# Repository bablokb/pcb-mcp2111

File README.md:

A small pcb for the MCP2221 chip
================================

The MCP2221 chip is an USB to GPIO bridge and brings GPIOs (including I2C) to any computer.

This github-repository contains a Kicad-project for the chip:

Status
------

Current status: the pcb was successfully produced
by [https://aisler.net](https://aisler.net):

Hardware
--------

Components for the board:

  - MCP2221/MCP2221A
  - socket
  - two capacitors (required, see datasheet)
  - a micro-sd-female connector (breakout)
  - an AMS1117 5V->3.3V converter (breakout, configurable using jumper-shim)
  - pullups for I2C-pins
  - pullups for GP0-GP3 (configurable using jumper-shims)
  - LEDs for GP0 and GP1 (configurable using jumper-shims)
  - buttons for GP2 and GP3
  - two male-connectors exposing all pins of the MCP2221 (breadboard-friendly spacing)

You can find details in the file `part-list.ods`.

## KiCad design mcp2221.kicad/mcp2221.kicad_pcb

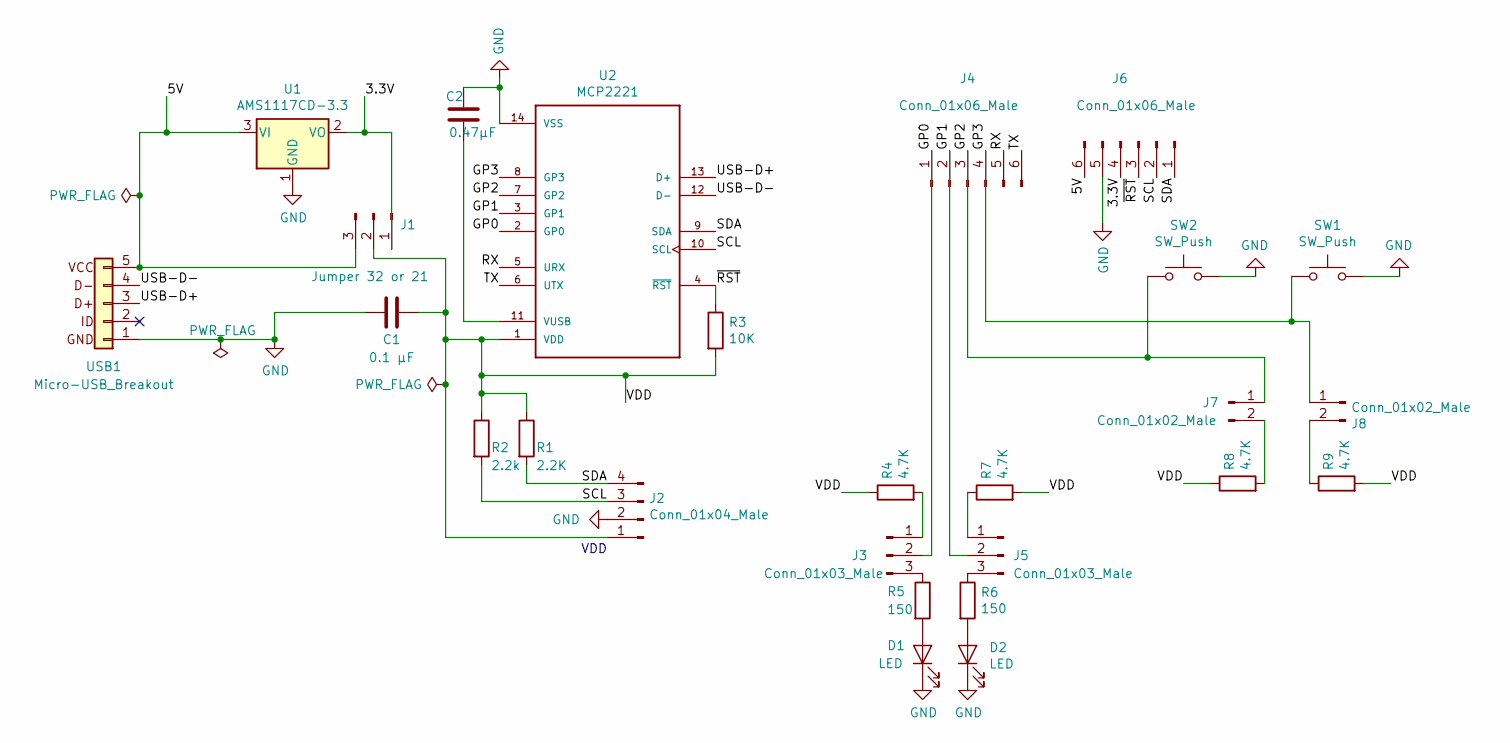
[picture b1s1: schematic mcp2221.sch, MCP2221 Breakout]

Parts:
C1: 0.1 µF; C_1206_3216_Pad1.7x1.75mm_BB
C2: 0.47µF; C_1206_3216_Pad1.7x1.75mm_BB
D1, D2: LED; LED_1206_3216_Pad1.7x1.75mm_BB
J1: Jumper 32 or 21; PinHeader_1x03_P2.54mm_Vertical
J2: Conn_01x04_Male; PinHeader_1x04_P2.54mm_Vertical
J3, J5: Conn_01x03_Male; PinHeader_1x03_P2.54mm_Vertical
J4, J6: Conn_01x06_Male; PinHeader_1x06_P2.54mm_Vertical
J7, J8: Conn_01x02_Male; PinHeader_1x02_P2.54mm_Vertical
R1: 2.2K; R_1206_3216_Pad1.7x1.75mm_BB
R2: 2.2k; R_1206_3216_Pad1.7x1.75mm_BB
R3: 10K; R_1206_3216_Pad1.7x1.75mm_BB
R4, R7, R8, R9: 4.7K; R_1206_3216_Pad1.7x1.75mm_BB
R5, R6: 150; R_1206_3216_Pad1.7x1.75mm_BB
SW1, SW2: SW_Push; SW_Push_1P1T_NO_6x6mm_H9.5mm
U1: AMS1117CD-3.3; AMS1117_Breakout
U2: MCP2221
USB1: Micro-USB_Breakout

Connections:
/3.3V: J1.1, J6.4, U1.2 (VO)
/5V: J1.3, J6.6, U1.3 (VI), USB1.5
/GP0: J3.2, J4.1, U2.2 (GP0)
/GP1: J4.2, J5.2, U2.3 (GP1)
/GP2: J4.3, J7.1, SW2.1, U2.7 (GP2)
/GP3: J4.4, J8.1, SW1.1, U2.8 (GP3)
/RX: J4.5, U2.5 (URX)
/SCL: J2.3, J6.2, R2.2, U2.10 (SCL)
/SDA: J2.4, J6.1, R1.2, U2.9 (SDA)
/TX: J4.6, U2.6 (UTX)
/USB-D+: U2.13 (D+), USB1.3
/USB-D-: U2.12 (D-), USB1.4
/VDD: C1.1, J1.2, J2.1, R1.1, R2.1, R3.2, R4.1, R7.2, R8.1, R9.2, U2.1 (VDD)
/~RST~: J6.3, R3.1, U2.4 (~RST~)
GND: C1.2, C2.2, D1.1 (K), D2.1 (K), J2.2, J6.5, SW1.2, SW2.2, U1.1 (GND), U2.14 (VSS), USB1.1
unnamed: C2.1, U2.11 (VUSB)
unnamed: D1.2 (A), R5.2
unnamed: D2.2 (A), R6.2
unnamed: J3.1, R4.2
unnamed: J3.3, R5.1
unnamed: J5.1, R7.1
unnamed: J5.3, R6.1
unnamed: J7.2, R8.2
unnamed: J8.2, R9.1

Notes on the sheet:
VDD

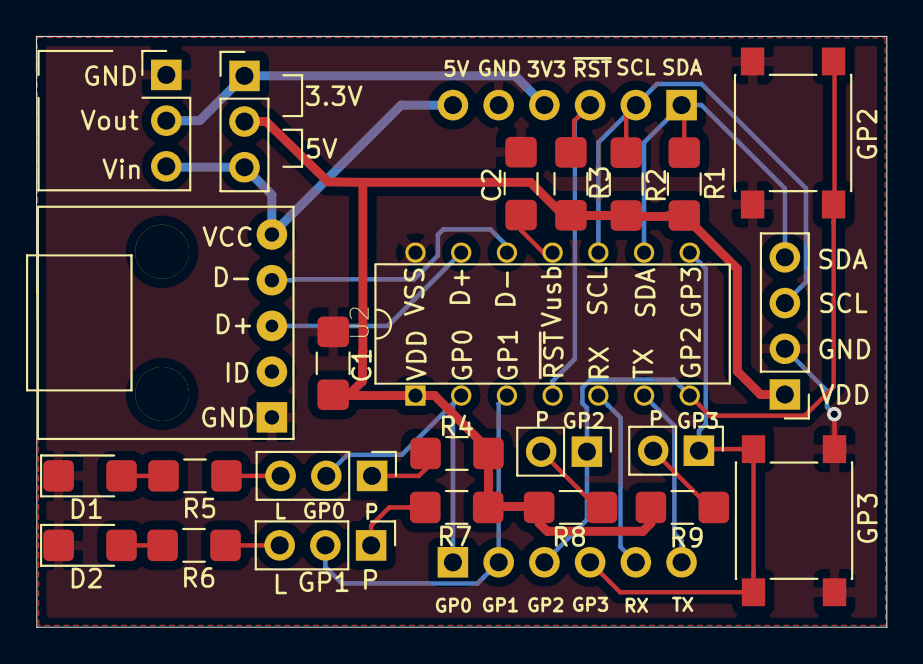
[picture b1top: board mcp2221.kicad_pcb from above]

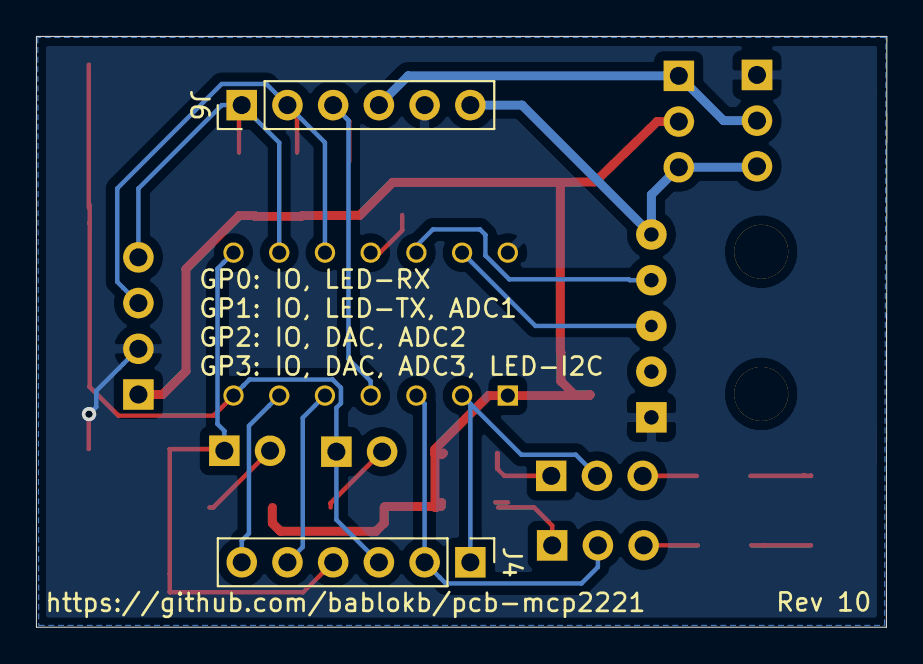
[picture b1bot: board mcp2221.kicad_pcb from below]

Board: 2 copper layers, 47.2 x 32.8 mm, 26 parts (2 on the bottom side), 24 nets.

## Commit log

2020-03-06 added basic description of project
2020-03-06 update link to github-repository
2020-03-08 fixed name MCP2221 instead of MCP2111
2020-03-10 replaced 4-pin USB-connector with 5-pin connector
2020-03-11 Rev 4: added pullups for all GPs, added SW1 to GP3
2020-03-24 added footprints, created initial pcb
2020-04-05 pcb layout changes
2020-04-09 Rev 6: switched to SMD, added connector, minor tweaks
2020-04-09 updated vor Rev 6
2020-04-09 initial layout for SMD
2020-04-10 added text on F.Silks
2020-04-11 updated footprint of AMS1117
2020-04-11 changed track width of power-tracks
2020-04-11 moved C2 and R1-R3 to MCP2221
2020-04-11 added labels
2020-04-11 fine-tuned labels
2020-04-14 make distance between connectors a multiple of 2.54 / optimize layout
2020-04-14 Rev 7: added button for GP2
2020-04-14 optimized labels
2020-04-17 changed to larger pads on SMD-footprints
2020-04-17 changed I2C-connector
2020-04-18 changed revision-number to 8
2020-04-18 updated to reflect current version
2020-04-18 optimzed labels
2020-04-18 added description of GPs on back of pcb
2020-04-18 updated status, added component-list
2020-04-30 Rev 9: don't connect Vusb to 3.3V / changed R for LEDs to 150
2020-04-30 fixed labels
2020-05-01 Rev 10: fix order of D-/D+ in schematic+pcb
2020-05-16 embed images
